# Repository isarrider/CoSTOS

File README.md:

# CoSTOS

**Controller for Solar Thermal – Open Source**

CoSTOS is an open-source controller for solar thermal systems: the box that
decides when the solar pump runs, how fast, and when it has to stop to
protect the store and the collector. It runs on a Linux single-board
computer (Raspberry Pi 3, 4 or 5), is written in Rust, and is
configured completely through a web interface.

> **Status: early development.** Milestone 1 has started: the control
> core and the safety supervisor exist as tested Rust libraries, nothing
> talks to hardware yet. Don't use this to control a real system. When it
> is ready to be tested, this README will say so.

## Why

Commercial solar controllers work, but they are closed: you can't see why
they decided something, you can't add a function, and getting data out of
them needs reverse-engineered protocols. CoSTOS is meant to be a controller
you can read, test and extend, with its data available everywhere you need
it.

The first goal is to replace a RESOL DeltaSol BX Plus in a real
installation, so that's the reference for which functions come first.

## Planned features

- **Solar control**: ΔT pump control with hysteresis, speed control for
  high-efficiency pumps (PWM), store maximum, collector emergency shutdown.
  Later: collector cooling, tube collector function, frost protection,
  heat quantity metering.
- **Sensors**: Pt1000 via an LTC2983 (up to 9 sensors on one chip, so
  the Pt1000s of an existing controller can stay) or a MAX31865 (one
  sensor, e.g. the collector), and DS18x20 1-Wire sensors (DS1820/DS18S20,
  DS18B20, DS1822). Mix them freely.
- **Web interface** for everything: live status, history, manual mode, and
  all configuration, including a setup wizard that shows live readings so
  you can identify sensors and test outputs. No config files to edit.
  Status pages are readable without login, any change needs one.
- **Data**: every value pushed to VictoriaMetrics once per second, buffered
  on disk while the database is unreachable and backfilled afterwards.
  Optional (off by default): MQTT with Home Assistant discovery.
- **Safety first**: outputs off by default, hardware and software
  watchdogs, plausibility checks on every sensor, and a safety layer that
  can only switch things off, never on. See
  [Safety](docs/ARCHITECTURE.md#4-safety).

## Hardware (planned)

- Raspberry Pi 4 or Raspberry Pi 5 with its own USB-C power supply, or a
  Raspberry Pi 3 B / B+ with its micro-USB supply (should work, untested;
  [details](docs/HAT-1wire.md#raspberry-pi-3))
- The [CoSTOS HAT](docs/HAT.md) (1-Wire edition or PT edition;
  [which one?](docs/HAT.md#which-hat-both-editions-compared)), or for a bench setup: an LTC2983 or MAX31865 for Pt1000
  sensors, a 4.7 kΩ pull-up for DS18x20 sensors
- **A high-efficiency pump with a PWM input in the solar profile** (Wilo
  PWM2 / iPWM2 such as the Wilo Yonos PARA ST …/iPWM2, Grundfos profile
  C). This is a safety requirement: the pump stays permanently on 230 V
  and is started, regulated and stopped over PWM, and with the solar
  profile a missing signal means *stop*, so any failure of the Pi or the
  HAT stops the pump. A feedback output (iPWM) is recommended. Pumps with
  a heating profile or without PWM need a cut-off relay on the HAT's
  optional relay output. Details:
  [Pump requirement](docs/ARCHITECTURE.md#pump-requirement-safety)
- An independent overtemperature cut-out on the store. CoSTOS does not
  replace that.

Mains wiring belongs in the hands of a qualified electrician.

## Documentation

- [Architecture](docs/ARCHITECTURE.md): goals, safety concept, hardware,
  software structure, web interface, data export, testing and the
  migration plan.
- [Hardware needed](docs/HARDWARE.md): parts lists and build instructions,
  starting with the PWM pump output.
- [HAT](docs/HAT.md): the plug-on board that combines all of it: the
  editions compared, and which one to choose.
  - [1-Wire edition](docs/HAT-1wire.md) (1 Pt1000 + two 1-Wire buses): the
    board as it will be built, wiring, costs.
  - [PT edition](docs/HAT-PT.md) (8 Pt1000 + one 1-Wire bus, for
    installations that keep their existing sensors).
- [HAT development](docs/HAT-development.md): why the HAT is built this
  way: decisions D1–D25, the alternatives that were dropped, the
  simulations, the rev A prototype and its bring-up and tests.
- [Reference installation](docs/installation.md): the system CoSTOS is
  built to control first.

## Code

A Cargo workspace (layout: [ARCHITECTURE 6.1](docs/ARCHITECTURE.md#61-workspace-layout)).
So far:

| Crate | What it does | Status |
|---|---|---|
| `crates/costos-core` | Control logic, `no_std`: temperature, time, sensor and duty types (the rules of ARCHITECTURE 6.1); ΔT control with the flow/return switch-off, store maximum, speed control (PI or BX-like steps), start profiles, anti-seize run and full-speed purge, and the control cycle that chains them | 🟢 milestone 1 done |
| `crates/costos-safety` | Safety supervisor, `no_std`: sensor unknown → off, collector and store emergency shutdown with hysteresis and latch, minimum off time; can only reduce the request | 🟢 milestone 1 done |
| `crates/costos-replay` | PC tool: replays recorded BX Plus days (`tests/replay`) through the control and lists where CoSTOS decides differently | 🟢 |
| `crates/costos-cycle` | One control second, `no_std`: sensor offsets, plausible ranges, control chain, inhibit, safety supervisor, plausibility checks, heat counter. The daemon and the simulation both call it | 🟢 |
| `crates/costos-sim` | Thermal model of the reference solar loop and closed-loop scenario tests of the whole control second (sunny, cloudy, stagnation, sensor faults and offsets, stuck pump, restarts) | 🟢 milestone 2 done |
| `crates/costos-config` | The settings document (strict JSON, validated by the control crates' own checks), generic and reference defaults ([`reference.json`](crates/costos-config/reference.json)), revision store with atomic writes, restore and fallback | 🟡 milestone 4 started |
| `crates/costosd` | The daemon: settings and counters from the state directory, the control loop against a backend (for now the simulator, real time or accelerated), status lines, logged interventions and alarms | 🟡 skeleton, simulator only |
| `tools/sim` | ngspice circuit simulations of the HAT, and the Python yield simulation (ARCHITECTURE 8.2) | 🟢 |

```sh
cargo test --workspace                                   # unit, property, replay and simulation tests
cargo clippy --workspace --all-targets -- -D warnings    # lints as in CI
cargo run --release -p costosd -- --state-dir /tmp/costos --days 3 --status-every 3600
                                                         # three simulated days through the daemon
```

CI also builds `costos-core`, `costos-safety` and `costos-cycle` for a
bare-metal RISC-V target, so they stay free of `std`.

## Contributing

Please read [CONTRIBUTING.md](CONTRIBUTING.md) first, whether you are a
person or an AI assistant: the rules for the control and safety code
(`no_std`, no panics, the supervisor only reduces), comments, tests,
commits and docs.

## Related

- [vbus2influx](https://github.com/isarrider/vbus2influx): reads a RESOL
  controller over VBus and pushes the data to InfluxDB/VictoriaMetrics.
  CoSTOS uses the same metric names (with the prefix `costos`), so
  dashboards carry over.

## License

[MIT](LICENSE)

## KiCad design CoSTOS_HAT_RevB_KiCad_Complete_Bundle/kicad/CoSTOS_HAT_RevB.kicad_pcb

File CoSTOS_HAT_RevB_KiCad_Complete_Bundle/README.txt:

===============================================================================
CoSTOS 1-Wire HAT — Rev B/D/E (DG350 8P Fixed Screw) Complete Engineering Bundle
Generated: 2026-11-27 | Target EDA: KiCad 6/7/8/9/10 | SPICE: ngspice 39-44+
===============================================================================

FOLDER STRUCTURE
----------------
1. kicad/   — Complete KiCad Hierarchical Project (177 parts, 83 nets)
   - CoSTOS_HAT_RevB.kicad_pro               <-- OPEN THIS FILE IN KICAD (6, 7, 8, 9, or 10)!
   - CoSTOS_HAT_RevB.kicad_sch               Root sheet linking all 6 circuit sheets
   - 01_Pt1000_Collector.kicad_sch       Sheet 2: Pt1000 Rev D 100% Basic Core + J6 DG350 8P Fixed Screw (PT1 + 1W-A/B) (31 parts)
   - 02_Pump_Supply.kicad_sch            Sheet 3: Pump Supply Rev E Option 2 CMOS (15 parts)
   - 03_Hardware_Watchdog.kicad_sch      Sheet 4: Dual-Schmitt Watchdog Rev B + Q12 +5V_REL switch (27 parts)
   - 04_OneWire_Buses.kicad_sch         Sheet 5: 5V 2N7002 1-Wire Buses A & B (21 parts -> J6:3-8)
   - 05_Output_Stage.kicad_sch           Sheet 6: Class-B PWM, FB1/RB1 & Populated REL1 SMD (35 parts; J4 THT opt.)
   - 06_Power_Entry.kicad_sch            Sheet 7: 40-Pin Pi Header + D18 Direct +5V_HAT + NT1 + FID1-3 (16 parts)
   - CoSTOS_HAT_RevB.kicad_pcb               FULLY PLACED, 2-LAYER ROUTED & PRE-FILLED 65x56 mm HAT
                                         Contains real KiCad-computed (filled_polygon ...) blocks for BOTH
                                         Priority-2 AGND and Priority-1 GND B.Cu copper zones — NOT just "press B"!
   - CoSTOS_HAT_RevB_KiCad_DRC_Report.rpt    Verbatim real KiCad 6.0.11 pcbnew WriteDRCReport proof:
                                         0 unconnected items, 0 DRC violations, 0 footprint errors!
   - CoSTOS_HAT_RevB.net                     Complete S-expression netlist (177 parts, 83 nets)

2. jlcpcb/  — 100% Live-Audited JLCPCB Economic PCBA Manufacturing Files (ZERO Placeholders, EUR 0.00 Ext Fees!)
   - CoSTOS_HAT_RevB_JLCPCB_BOM.csv          Populated SMD only (160 parts, 33 reels):
                                         32 Basic + 1 Preferred (C17656) + 0 Extended = EUR 0.00 Ext fees!
                                         Every line includes live-verified LCSC #, Manufacturer Part (MPN),
                                         Value, Tolerance, Package, and JLCPCB Class (Basic/Preferred),
                                         including C7955 (LM393DR2G Basic), C105432 (S8550 Basic), C181103 (TL431 Basic),
                                         C46653 (1nF X7R Basic), C1710 (10nF X7R Basic for C101/C102/C9), C17513 (7x 1.00k 1% Basic),
                                         C49678 (100nF 50V ESD on EVERY Pt1000 wire: C106/C105), and C81598 (D8/D8B symmetric clamp).
   - CoSTOS_HAT_RevB_Full_Master_BOM.csv     All 177 populated parts (SMD + THT) + DNP table

3. spice/   — Official Vendor TI LM393 ngspice-39 Verification Suites (0 Warnings)
   - CoSTOS_HAT_RevB_Full_Sim.cir            Full-board transient + 6-pt Pt1000 sweep (-20..+250C/OPEN/SHORT)
                                         + Populated REL1 SMD (67 mA coil, 123.2 mA short, 5.31 V flyback, 2.2 uV WD cutoff)
                                         + +3V3_ANA AC filter (-36.04 dB @ 100 kHz) using the official vendor
                                         Texas Instruments / MicroSim .SUBCKT LM393 macromodel (C7955).
                                         Run: ngspice -b CoSTOS_HAT_RevB_Full_Sim.cir
   - CoSTOS_HAT_RevB_Watchdog_RealTime.cir   REAL-TIME UNSCALED Hardware Watchdog verification (ZERO time scaling!):
                                         Exact BOM values (R301=4.7k, C16=100n, C17/C19=1u, C18=38u, R49||R50=500k)
                                         with official TI .SUBCKT LM393 & Basic S8550 Q15:
                                           Test 1 (36 s real time, 20 Hz HB -> halt @ 10 s):
                                             Q12 +5V_REL cutoff = 16.11 s (5.046 V -> 2.2 uV), PUMP1 WD_OK cutoff = 18.42 s
                                           Test 2 (4 s real time, 1 kHz runaway loop):
                                             V(wd_cap) max = 0.745 V (< 1.54 V threshold -> +5V_REL & WD_OK stay tripped!)
                                         Run: ngspice -b CoSTOS_HAT_RevB_Watchdog_RealTime.cir

4. docs/    — Complete PDF Engineering Report Pack (7 Reports)
   - 01_Pt1000_Collector_Report.pdf
   - 02_Pump_Supply_Report.pdf
   - 03_Hardware_Watchdog_Report.pdf
   - 04_OneWire_Buses_Report.pdf
   - 05_Output_Stage_Report.pdf
   - 06_Power_Entry_Report.pdf
   - 07_Full_HAT_Costs_BOM_Report.pdf

PT1000 ACCURACY & HONEST 100% BASIC REEL COMPARISON (VS. D25 MAX31865)
----------------------------------------------------------------------
- Locked 100% Basic Bridge (7x C17513 1.00k +/-1% +/-100ppm Basic = 4.00k / 1.00k / 2.00k + C1710 10nF X7R + C49678 100nF 50V ESD on EVERY Pt1000 wire + D8/D8B 1N4148W):
  0 Extended SMD reels across the ENTIRE HAT = EUR 0.00 SMD loading fees!
  Raw uncalibrated accuracy is ~+/-2-4 K (ideal for roof solar collector differential delta-T), tightening to
  ~+/-0.4-0.6 K year-round after a one-time 5-second software calibration in the Setup Wizard (tap water / DS18B20).
- Optional Drop-In 0.1% Upgrade (no PCB change): Swap C17513 -> C110774 (1.00k 0.1% +/-25ppm, +EUR 2.80 Ext) for +/-0.69 K RSS out-of-the-box without calibration.
- Baseline D25 MAX31865 + 4.30k 0.1% ref:
  2-3 Extended reels (MAX31865 + 4.30k 0.1% + PESD24V = EUR 8.40) -> +/-0.59 K worst-case (bench-proven SPI IC).
- Status: The U1 LM393DR2G RC-ramp + 2-pt BIST circuit is SPICE-verified with the official TI
  LM393 macromodel, but NOT yet bench-proven on physical hardware against a MAX31865 reference.

LOCKED ARCHITECTURE DECISIONS VS. COSTOS REPO D18 / D25
-------------------------------------------------------
1. REL1 SMD Driver Populated; J4 2-Pin THT Optional [NOW MATCHED TO D25]
   - All REL1 SMD parts (Q10 AO3400A, Q12 AO3401A, Q11 MMBT3904, D6 SS14, D7 Green LED, R15 10k,
     R17 2.2k, R501A||B = 2x 10R Basic = 5.0R / 123.2 mA short limit) are factory-populated
     (0 new reels, EUR 0.00 extra feeder fee, +EUR 0.23/bd). Only J4 THT screw block is optional.
2. Direct Pi +5V -> +5V_HAT (Foldback eFuse Dropped) + 100% Basic SMD Optimization [MATCHED TO D18]
   - Removed eFuse (C15545) + consolidated ALL 12 Extended reels -> 0 Extended reels (EUR 0.00 SMD loading fees, -EUR 33.60/order!).
3. 1-Wire at 5 V via 2N7002 level-shifters + Basic TL431 5.36 V clamp [LOCKED — 1-Wire Edition]
   - Gives 5 V bus swing, 40-65 m DS18B20 reach, and tighter 5.390 V +12 V DQ clamp (+EUR 0.23/bd, EUR 0.00 Ext fee).
4. Plain 11 mm non-stacking 40-pin Pi header (J1) [LOCKED — Turnkey JLCPCB THT]
   - EUR 0.45 low-profile header clearing passive Pi 5 heatsinks; wave-soldered by JLCPCB Standard PCBA.
5. Combined 8-pin J6 sensor terminal (DG350-3.5-08P / Dual-Tier DG350D-3.5-08P) [LOCKED — Turnkey JLCPCB THT]
   - 0 mm overhang and only 3 factory-soldered THT parts (J1, J2, J6); rising-cage M2 screw clamps.
6. Discrete LM393DR2G (C7955) 72 Hz RC Ramp + 100% Basic Bridge (C17513 / C1710 / C49678 / D8+D8B) [LOCKED — Validate on 2x Prototype]
   - Keeps SPI0/I2C1 free, achieves EUR 0.00 SMD loading fees, & saves EUR 4.50+/bd (1-Wire) or EUR 38+/bd (8-ch All-Pt1000) vs MAX31865;
     requires 2x bench validation against MAX31865 before volume production.

UNPOPULATED OPTIONS (DNP / n.f. — Footprint Only, EUR 0.00 BOM Cost)
--------------------------------------------------------------------
- J4 (2-pin 3.5 mm THT connector only — REL1 SMD driver IS populated), J3 (PUMP2), J5 (REL2), U_ID (CAT24C32 EEPROM), U10 (DS2482-800)

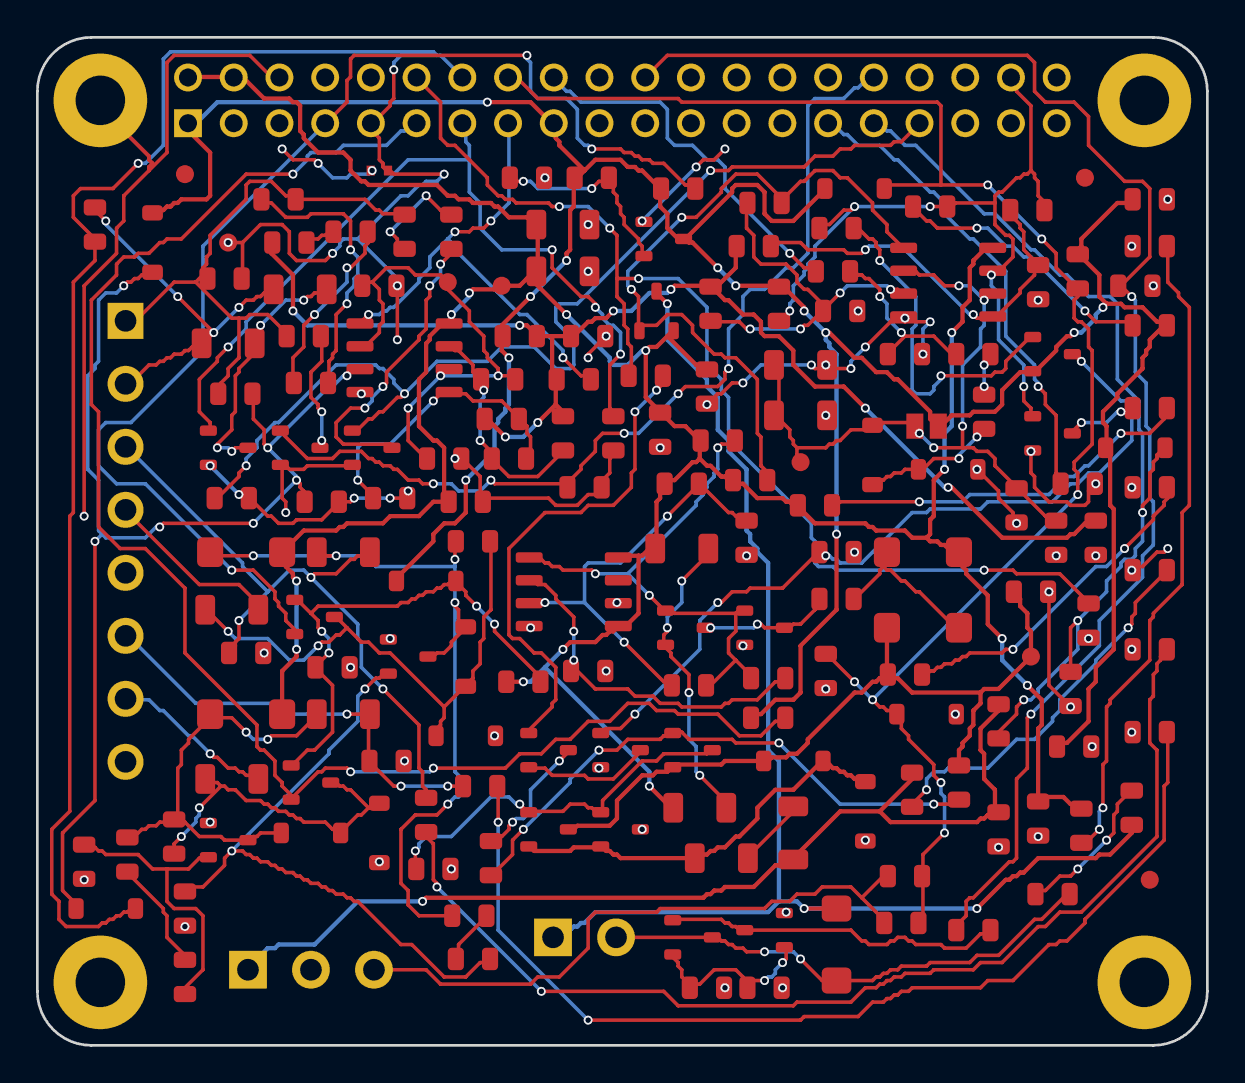
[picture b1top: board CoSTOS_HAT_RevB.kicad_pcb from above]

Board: 2 copper layers, 65.0 x 56.0 mm, 178 parts (0 on the bottom side), 83 nets.

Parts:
C2A, C2B, C18A, C18B: 22 µF 25V X5R; C_1206_3216Metric
C9, C101, C102: 10 nF 50V X7R; C_0805_2012Metric
C16, C21, C24, C25, C26, C103, C104, C105, C106, C301, C601, C602, C603: 100 nF 50V X7R; C_0805_2012Metric
C17, C19: 1 µF 50V X7R; C_0805_2012Metric
C20: 1 nF 50V X7R; C_0805_2012Metric
C22: 4.7 µF 25V X5R; C_0805_2012Metric
C23, C604: 10 µF 25V X5R; C_0805_2012Metric
D2, D3, D7, D12, D33, D34, D35: Green LED 525nm; LED_0805_2012Metric
D4, D5, D8, D8B, D17, D18, D19, D20, D23, D24, D25, D27, D28, D30: 75V 150mA Fast Diode; D_SOD-123
D6, D21, D22, D26, D29: 40V 1A Schottky; D_SMA
D9, D31, D32: 2.495V–36V Shunt Reg; SOT-23
D36: Red LED 630nm; LED_0805_2012Metric
FID1, FID2, FID3: 1.0mm Fiducial (DNP); Fiducial_1mm_Mask2mm
H1, H2, H3, H4: M2.5×11mm Nylon; MountingHole_2.7mm_M2.5_Pad
J1: 2×20 11mm Header; PinSocket_2x20_P2.54mm_Vertical
J2: DG350-3.5-03P; TerminalBlock_Phoenix_MKDS-1,5-3_1x03_P3.50mm_Horizontal
J4: DG350-3.5-02P (DNP); TerminalBlock_Phoenix_MKDS-1,5-2_1x02_P3.50mm_Horizontal
J6: DG350-3.5-08P; TerminalBlock_Phoenix_MKDS-1,5-8_1x08_P3.50mm_Horizontal
JP1: 2-Pad Test Pt (DNP); SolderJumper-2_P1.3mm_Open_Pad1.0x1.5mm
NT1: AGND-GND Star Jumper; NetTie-2_SMD_Pad0.5mm
Q1, Q2, Q3, Q5, Q10, Q18, Q23: 30V 5.7A NMOS; SOT-23
Q4, Q6, Q11: 40V 200mA NPN; SOT-23
Q7, Q8, Q15: 25V 500mA PNP; SOT-23
Q12, Q17: -30V -4A PMOS; SOT-23
Q19, Q20: 60V 115mA NMOS; SOT-23
R1, R17, R22, R37, R314, R406, R407: 2.2 kΩ; R_0805_2012Metric
R7, R16, R19, R54, R56, R108, R313, R320, R323, R324: 100 kΩ; R_0805_2012Metric
R9A, R9B, R60A, R60B, R105A, R105B, R401, R402, R403, R404: 100 Ω (250mW); R_1206_3216Metric
R11, R31: 22 kΩ; R_0805_2012Metric
R12A, R12B, R35, R36, R38, R110, R111, R301, R410, R411, R604, R605: 4.7 kΩ; R_0805_2012Metric
R15, R32, R33, R61, R104, R112, R113, R114, R310, R311, R312, R408, R409, R412A, R413, R414A, R415, R606: 10 kΩ; R_0805_2012Metric
R49, R50: 1.0 MΩ; R_0805_2012Metric
R55, R321, R322: 47 kΩ; R_0805_2012Metric
R58: 15 kΩ; R_0805_2012Metric
R59, R305, R405, R412B, R414B: 1.5 kΩ; R_0805_2012Metric
R101A, R101B, R101C, R101D, R102, R103A, R103B: 1.00 kΩ; R_0805_2012Metric
R106, R107: 390 kΩ; R_0805_2012Metric
R109: 150 kΩ; R_0805_2012Metric
R325: 220 kΩ; R_0805_2012Metric
R501A, R501B, R602: 10 Ω; R_0805_2012Metric
TP1, TP2, TP3, TP4, TP5: 1.0mm Test Pad (DNP); TestPoint_Pad_D1.0mm
U1, U3, U4: LM393DR2G; SOIC-8_3.9x4.9mm_P1.27mm

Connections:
1W_A_5V_PROT: D24.1, D26.1, D31.3, R402.1, R406.1, R412A.1
1W_A_DQ: J6.4, R401.2
1W_A_DQ_INT: D24.2, D25.1, Q19.3, R401.1, R406.2
1W_A_LED_A: D34.2, R410.2
1W_A_PI: J1.7, Q19.2, R408.2
1W_A_R412_MID: R412A.2, R412B.1
1W_A_TL431_REF: D31.2, R412B.2, R413.1
1W_A_VDD: C25.1, J6.3, R402.2, R410.1
1W_B_5V_PROT: D27.1, D29.1, D32.3, R404.1, R407.1, R414A.1
1W_B_DQ: J6.7, R403.2
1W_B_DQ_INT: D27.2, D28.1, Q20.3, R403.1, R407.2
1W_B_LED_A: D35.2, R411.2
1W_B_PI: J1.11, Q20.2, R409.2
1W_B_R414_MID: R414A.2, R414B.1
1W_B_TL431_REF: D32.2, R414B.2, R415.1
1W_B_VDD: C26.1, J6.6, R404.2, R411.1
+3V3: C602.1, D3.2, D8.1, D9.3, D17.1, D18.1, D23.1, J1.1, J1.17, JP1.2, Q15.2, R11.1, R311.1, R408.1, R409.1, R602.1, R604.1, R605.1
+3V3_ANA: C603.1, C604.1, R101A.1, R107.1, R110.1, R111.1, R320.1, R323.1, R602.2
+5V_HAT: C2A.1, C2B.1, C21.1, C104.1, C301.1, C601.1, D21.2, D26.2, D29.2, J1.2, J1.4, Q12.2, R1.1, R54.1, R59.1, R60A.1, R60B.1, R310.1, R314.1, R405.1, TP1.1, U1.8, U3.5, U3.8, U4.8
+5V_REL: D6.1, D7.2, J4.1, Q12.3
+V_DRV: C23.1, D4.1, D22.1, Q6.3, Q8.2, R36.1, R61.1, TP2.1
AGND: C101.2, C102.2, C103.2, C104.2, C105.2, C106.2, D8B.2, J1.9, J1.14, NT1.2, Q1.2, R108.2, R112.2, R113.2, R114.2, TP5.1, U1.4
DRV_OSC: Q17.1, Q18.1, R56.2, R58.1, R59.2, U3.1
DRV_OSC_INN: C20.1, R58.2, U3.2
DRV_OSC_INP: R54.2, R55.1, R56.1, U3.3
DRV_PUMP_A: C22.2, D21.1, D22.2
DRV_P_SRC: Q17.2, R60A.2, R60B.2
DRV_SW: C22.1, Q17.3, Q18.3
DUTY_IN: J1.15, R110.2, U1.1
FB1: C9.1, D17.2, D30.1, J1.16, R11.2, R12A.2, R12B.2
FB1_EXT: J2.3, R12A.1, R12B.1
GND: C2A.2, C2B.2, C9.2, C16.2, C18A.2, C18B.2, C20.2, C21.2, C23.2, C24.2, C25.2, C26.2, C301.2, C601.2, C602.2, C603.2, C604.2, D2.1, D5.2, D9.1, D12.1, D20.2, D25.2, D28.2, D30.2, D31.1, D32.1, D33.1, D34.1, D35.1, H1.1, H2.1, H3.1, H4.1, J1.6, J1.20, J1.25, J1.30, J1.34, J1.39, J2.2, J6.5, J6.8, NT1.1, Q2.2, Q3.2, Q5.2, Q7.3, Q11.2, Q18.2, Q23.2, R7.2, R16.2, R19.2, R32.2, R37.2, R38.2, R49.2, R50.2, R55.2, R313.2, R321.2, R322.2, R413.2, R415.2, R501A.2, R501B.2, R604.2, R606.2, U3.4, U3.6, U4.4
PT1_B_EXT: C105.1, J6.2, R105A.1, R105B.1
PT1_B_SW: Q1.3, R105A.2, R105B.2
PT1_R101_1: R101A.2, R101B.1
PT1_R101_2: R101B.2, R101C.1
PT1_R101_3: R101C.2, R101D.1
PT1_SENSE: C103.1, D8.2, D8B.1, R104.2, U1.3
PT1_V_DIV: C106.1, J6.1, R101D.2, R102.1, R103A.1, R104.1
PT_OSC_OUT: R106.1, R109.1, R111.2, U1.7
PT_RAMP: C101.1, C102.1, R106.2, TP3.1, U1.2, U1.6
PT_RAMP_TH: R107.2, R108.1, R109.2, U1.5
PT_REF_HI: Q3.3, R103B.2
PT_REF_HI_MID: R103A.2, R103B.1
PT_REF_LO: Q2.3, R102.2
PT_SEL: J1.13, Q1.1, R112.1
PUMP1_LED_A: D12.2, R22.2
PUMP1_PWM_J2: J2.1, R9B.2, R22.1, R31.1, R38.1
PWM1: J1.12, R7.1, R33.1
PWM1_BASE: Q4.1, R33.2
PWM_AND_MID: Q4.2, Q5.3
PWM_NODE_DRV: Q6.1, Q7.1, Q8.3, R37.1
PWM_PUSH_OUT: D4.2, D5.1, Q6.2, Q7.2, R9A.1
PWM_Q4_COL: Q4.3, R35.1
PWM_R9_MID: R9A.2, R9B.1
PWR_LED_A: D2.2, R1.2
Q8_BASE: Q8.1, R35.2, R36.2
RB1: D18.2, J1.31, R31.2, R32.1
REF_HI_SEL: J1.33, Q3.1, R114.1
REF_LO_SEL: J1.32, Q2.1, R113.1
REL1: J1.22, R15.1, R16.1
REL1_GATE: Q10.1, Q11.3, R15.2
REL1_LED_K: D7.1, R17.1
REL1_OUT: D6.2, J4.2, Q10.3, R17.2
REL1_SNS: Q10.2, Q11.1, R501A.1, R501B.1
REL2_SPARE: J1.29, R19.1
V3V3_TL431_REF: D9.2, R605.2, R606.1
VDRV_LED_A: D33.2, R61.2
V_G_1W: C24.1, D23.2, Q19.1, Q20.1, R405.2
WD_CAP_MID: C17.2, C19.1
WD_FLT_LED_A: D36.2, R314.2
WD_FLT_LED_K: D36.1, Q23.3
WD_HB: J1.18, R301.1
WD_LED_K: D3.1, R305.1
WD_LPF: C16.1, C17.1, R301.2
WD_OK: Q5.1, Q15.3, R313.1
WD_PUMP: C19.2, D19.2, D20.1
WD_Q15_B: Q15.1, R312.2
WD_RB: J1.38, Q23.1, R305.2, R311.2, R312.1, R324.2, U4.7
WD_REL_N: Q12.1, R310.2, R325.2, U4.1
WD_U4A_TH: R320.2, R321.1, R325.1, U4.3
WD_U4B_TH: R322.1, R323.2, R324.1, U4.5
WD_VCAP: C18A.1, C18B.1, D19.1, JP1.1, R49.1, R50.1, TP4.1, U4.2, U4.6
